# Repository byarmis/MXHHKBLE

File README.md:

# MX-HHKBLE
Using the [nice!nano](https://docs.nicekeyboards.com/#/), making a low-profile MX-compatible HHKB.

# Key Switches
[Kailh low profile round switches](https://mechanicalkeyboards.com/shop/index.php?l=product_detail&p=6343)

# Hardware
* PCB
    * Working on that now
* [Switches](https://mechanicalkeyboards.com/search.php?keyword=choc+round)
* Keycaps
    * Any Cherry-compatible switches should work
    * Testing will be done with GMK caps
* [nice!nano](https://nicekeyboards.com/products/nice-nano-v1-0)
* [1N4148 Diodes](https://www.digikey.com/products/en/discrete-semiconductor-products/diodes-rectifiers-single/280?k=1n4148&k=&pkeyword=1n4148&sv=0&pv1291=404832&sf=1&FV=-8%7C280&quantity=&ColumnSort=0&page=1&pageSize=25)
* [Power switch](https://www.digikey.com/product-detail/en/nidec-copal-electronics/CUS-12TB/563-1102-1-ND/1124231)
* [Battery](https://www.sparkfun.com/products/13112)
    * Depending on the battery you get, you might need to swap the ground and positive leads
* [JST connector](https://www.sparkfun.com/products/9749)
* [Surface-mount female pins](https://www.digikey.com/en/products/detail/samtec-inc/SSM-113-L-SV/1106316)
* [Male pin headers](https://www.sparkfun.com/products/116)
* [Stabilizers](https://www.aliexpress.com/item/33039182740.html) 
    * Space bar (6.25u)
    * Left shift (2u)
    * Enter (2u)
* 3D-printed standoff legs (to be designed)
    * Screws and nuts, also to be determined

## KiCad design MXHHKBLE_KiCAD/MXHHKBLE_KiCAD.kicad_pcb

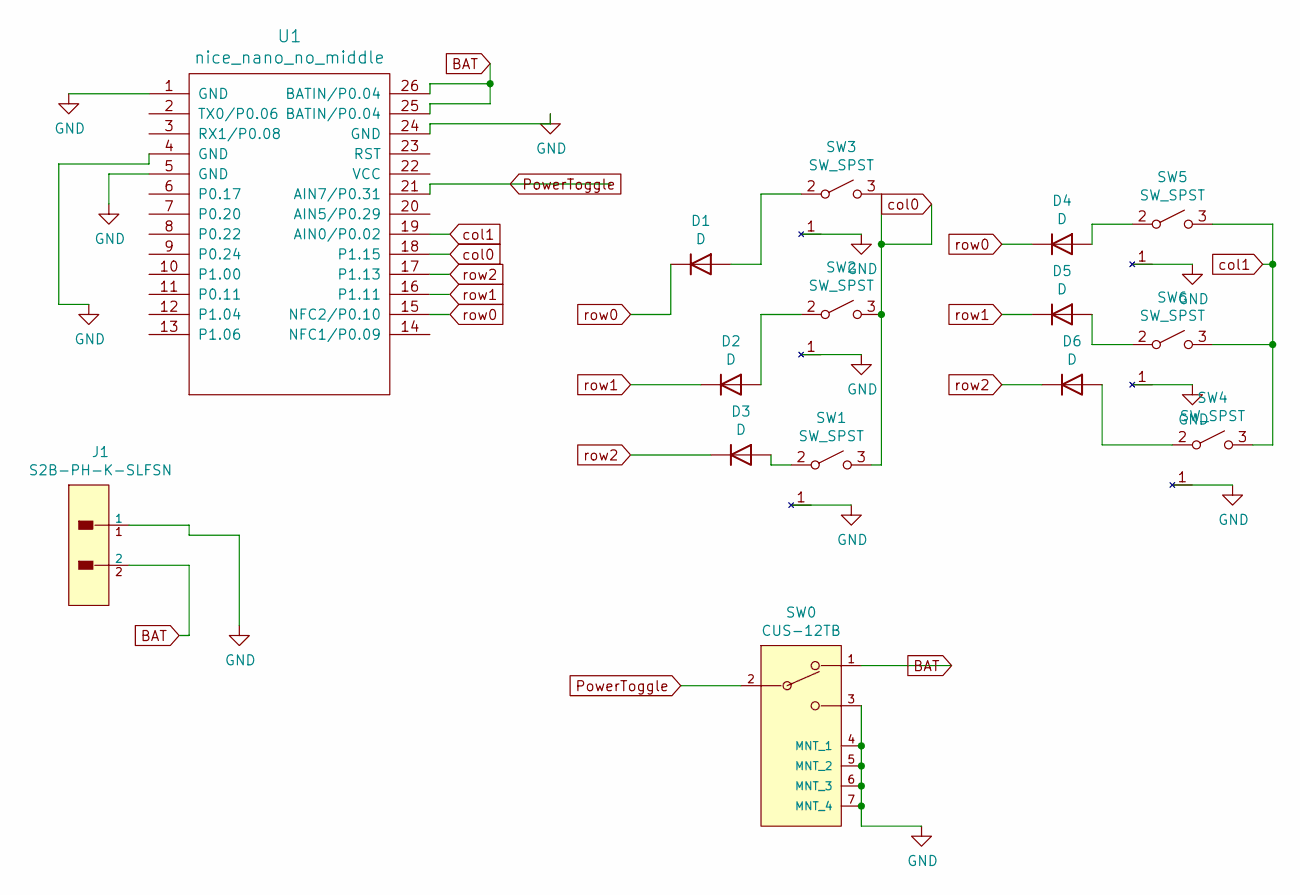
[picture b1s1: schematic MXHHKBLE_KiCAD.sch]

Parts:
D1, D2, D3, D4, D5, D6: D; D_SOD-123F
J1: S2B-PH-K-SLFSN; JST-S2B-PH-K-SLFSN-0-0-0; digikey description CONN HEADER PH SIDE 2POS 2MM
SW0: CUS-12TB; Nidec_Copal-CUS-12TB-MFG; voltage rating DC 4V; digikey description SWITCH SLIDE SPDT 300MA 4V
SW1, SW2, SW3, SW4, SW5, SW6: SW_SPST; Kailh_PG1353
U1: nice_nano_no_middle; nice_nano_no_middle_socket

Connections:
BAT: J1.2, SW0.1, U1.25 (BATIN/P0.04), U1.26 (BATIN/P0.04)
GND: J1.1, SW0.3, SW0.4 (MNT_1), SW0.5 (MNT_2), SW0.6 (MNT_3), SW0.7 (MNT_4), SW1.1 (NC), SW2.1 (NC), SW3.1 (NC), SW4.1 (NC), SW5.1 (NC), SW6.1 (NC), U1.1 (GND), U1.4 (GND), U1.5 (GND), U1.24 (GND)
unnamed: D1.2 (A), SW3.2 (A)
unnamed: D2.2 (A), SW2.2 (A)
unnamed: D3.2 (A), SW1.2 (A)
unnamed: D4.2 (A), SW5.2 (A)
unnamed: D5.2 (A), SW6.2 (A)
unnamed: D6.2 (A), SW4.2 (A)
PowerToggle: SW0.2 (C), U1.21 (AIN7/P0.31)
col0: SW1.3 (B), SW2.3 (B), SW3.3 (B), U1.18 (P1.15)
col1: SW4.3 (B), SW5.3 (B), SW6.3 (B), U1.19 (AIN0/P0.02)
row0: D1.1 (K), D4.1 (K), U1.15 (NFC2/P0.10)
row1: D2.1 (K), D5.1 (K), U1.16 (P1.11)
row2: D3.1 (K), D6.1 (K), U1.17 (P1.13)

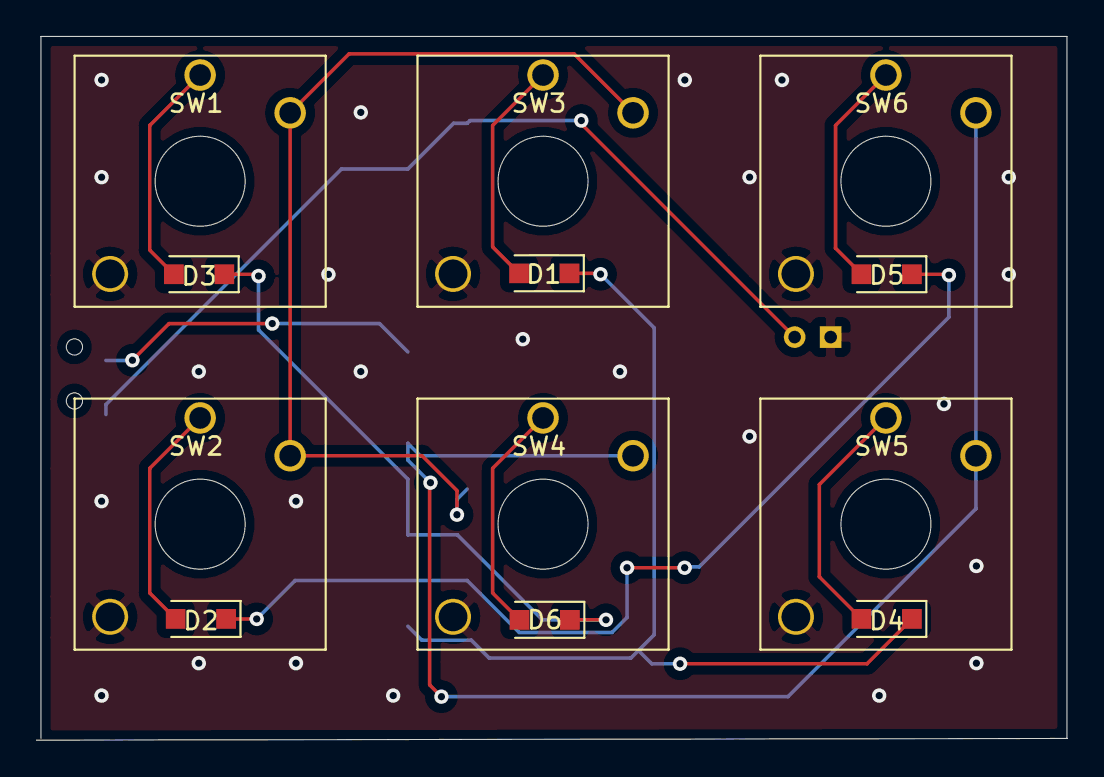
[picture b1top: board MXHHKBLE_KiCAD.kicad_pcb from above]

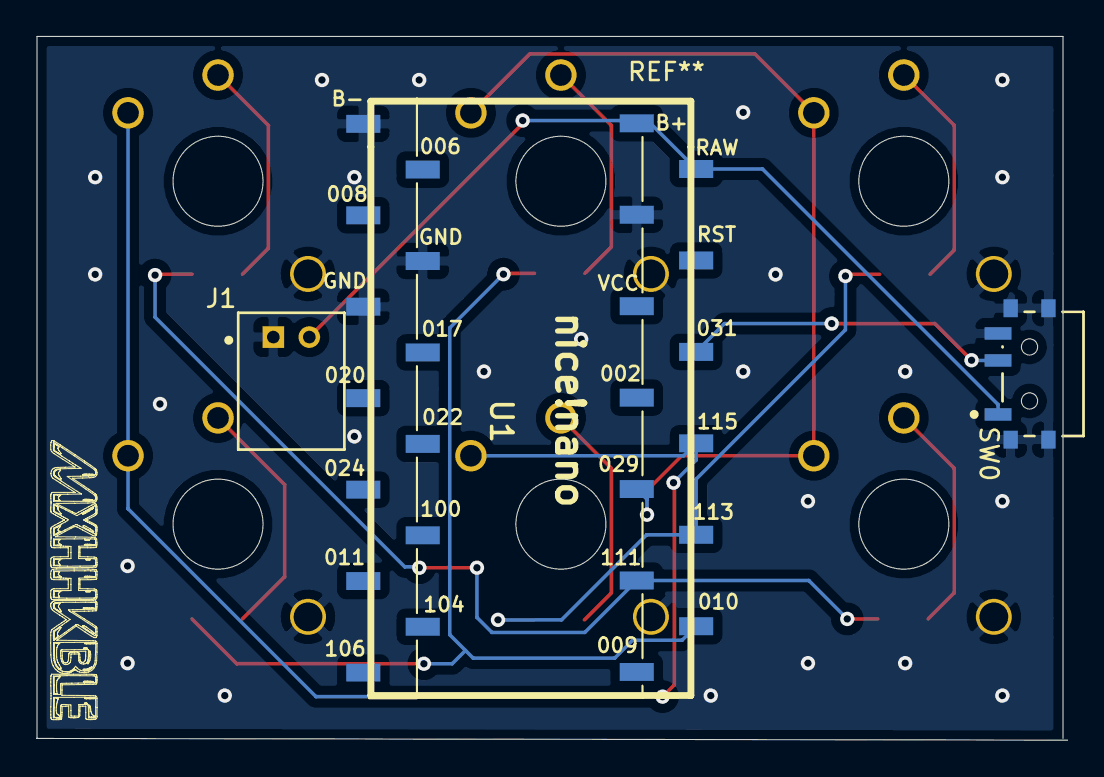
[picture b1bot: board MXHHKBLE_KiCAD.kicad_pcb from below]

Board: 2 copper layers, 57.3 x 39.1 mm, 15 parts (3 on the bottom side), 14 nets.

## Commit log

2020-09-18 Uploaded initial data sheets
2020-09-18 JST Connector datasheet
2020-09-18 Diode and pin header datasheet
2020-09-18 Datasheet organization
2020-09-18 README tweaks
2020-09-18 Added links to hardware
2020-09-18 Power switch
2020-09-21 SMD headers since through hole won't fit
2020-09-21 Macropad test
2020-10-04 Macro pad update
